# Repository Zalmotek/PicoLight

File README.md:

# PicoLight 🌈

✨ PicoLight is a minimalist adjustable light for low-light photography, based on the Raspberry Pi Pico.

✨ For more details check out the project documentation on [Hackaday](https://hackaday.io/project/182069-picolight-minimalist-light-for-product-shots).

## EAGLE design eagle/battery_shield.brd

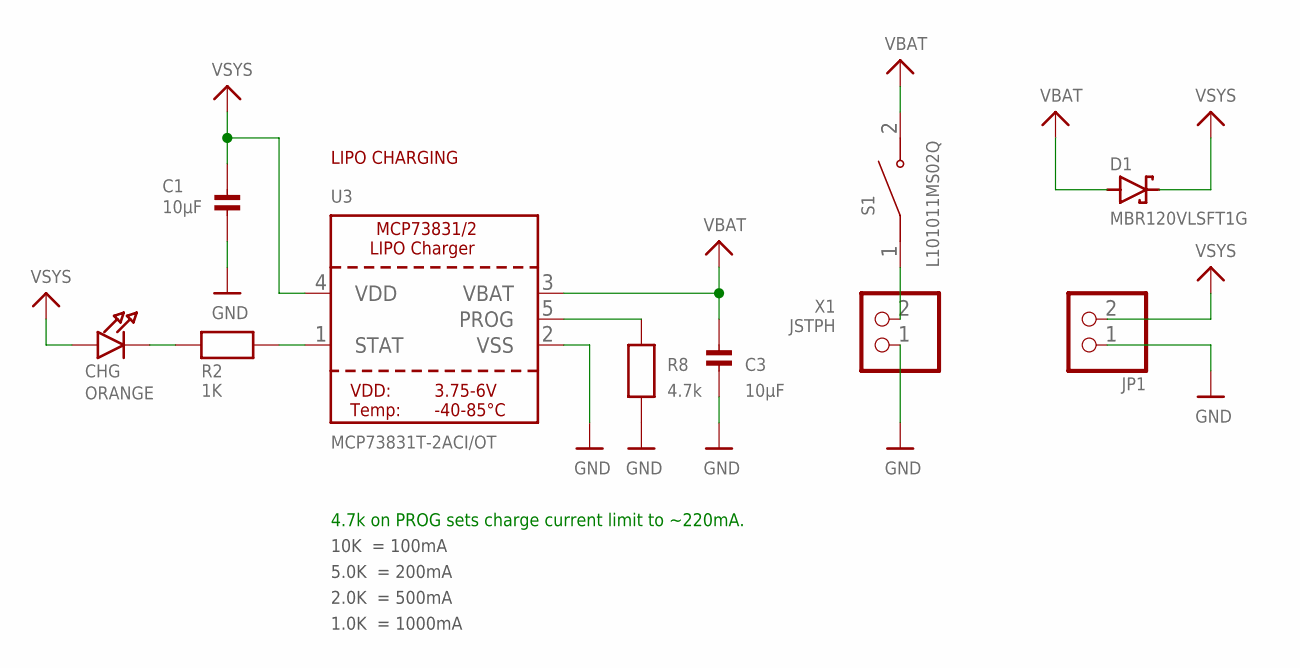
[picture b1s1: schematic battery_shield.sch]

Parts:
C1, C3: 10µF; 0805-NO
CHG: ORANGE; CHIPLED_0805_NOOUTLINE
D1: MBR120VLSFT1G; SOD123FL
JP1: PINHD-1X2; 1X02
R2: 1K; 0603-NO
R8: 4.7k; 0603-NO
S1: L101011MS02Q; SW_L101011MS02Q
U3: MCP73831T-2ACI/OT; SOT23-5
X1: JSTPH; JSTPH2

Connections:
GND: C1.2, C3.2, JP1.1, R8.2, U3.2 (VSS), X1.1
unnamed: CHG.C, R2.1
unnamed: S1.1, X1.2
unnamed: R2.2, U3.1 (STAT)
unnamed: R8.1, U3.5 (PROG)
VBAT: C3.1, D1.A, S1.2, U3.3 (VBAT)
VSYS: C1.1, CHG.A, D1.C, JP1.2, U3.4 (VDD)

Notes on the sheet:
10K = 100mA
5.0K = 200mA
2.0K = 500mA
1.0K = 1000mA
LIPO CHARGING
4.7k on PROG sets charge current limit to ~220mA.

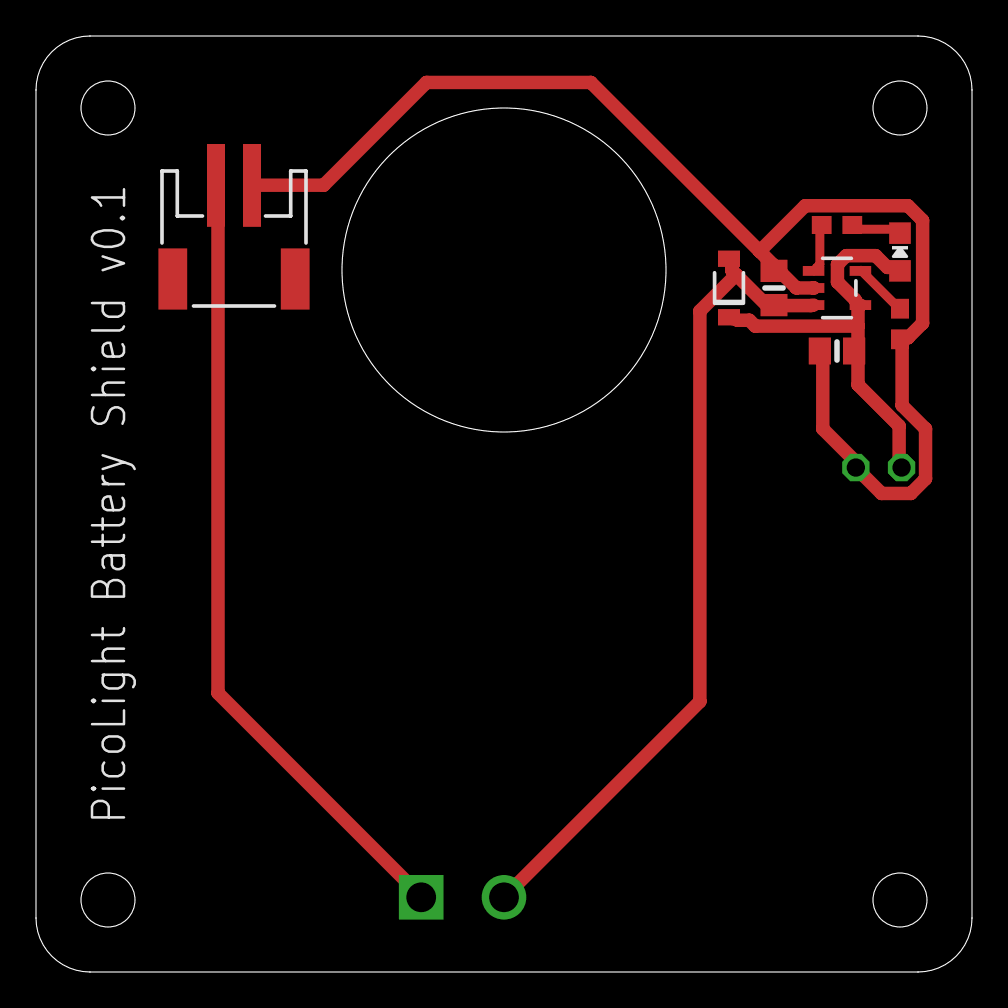
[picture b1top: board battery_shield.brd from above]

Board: 2 copper layers, 52.0 x 52.0 mm, 10 parts (1 on the bottom side), 7 nets.

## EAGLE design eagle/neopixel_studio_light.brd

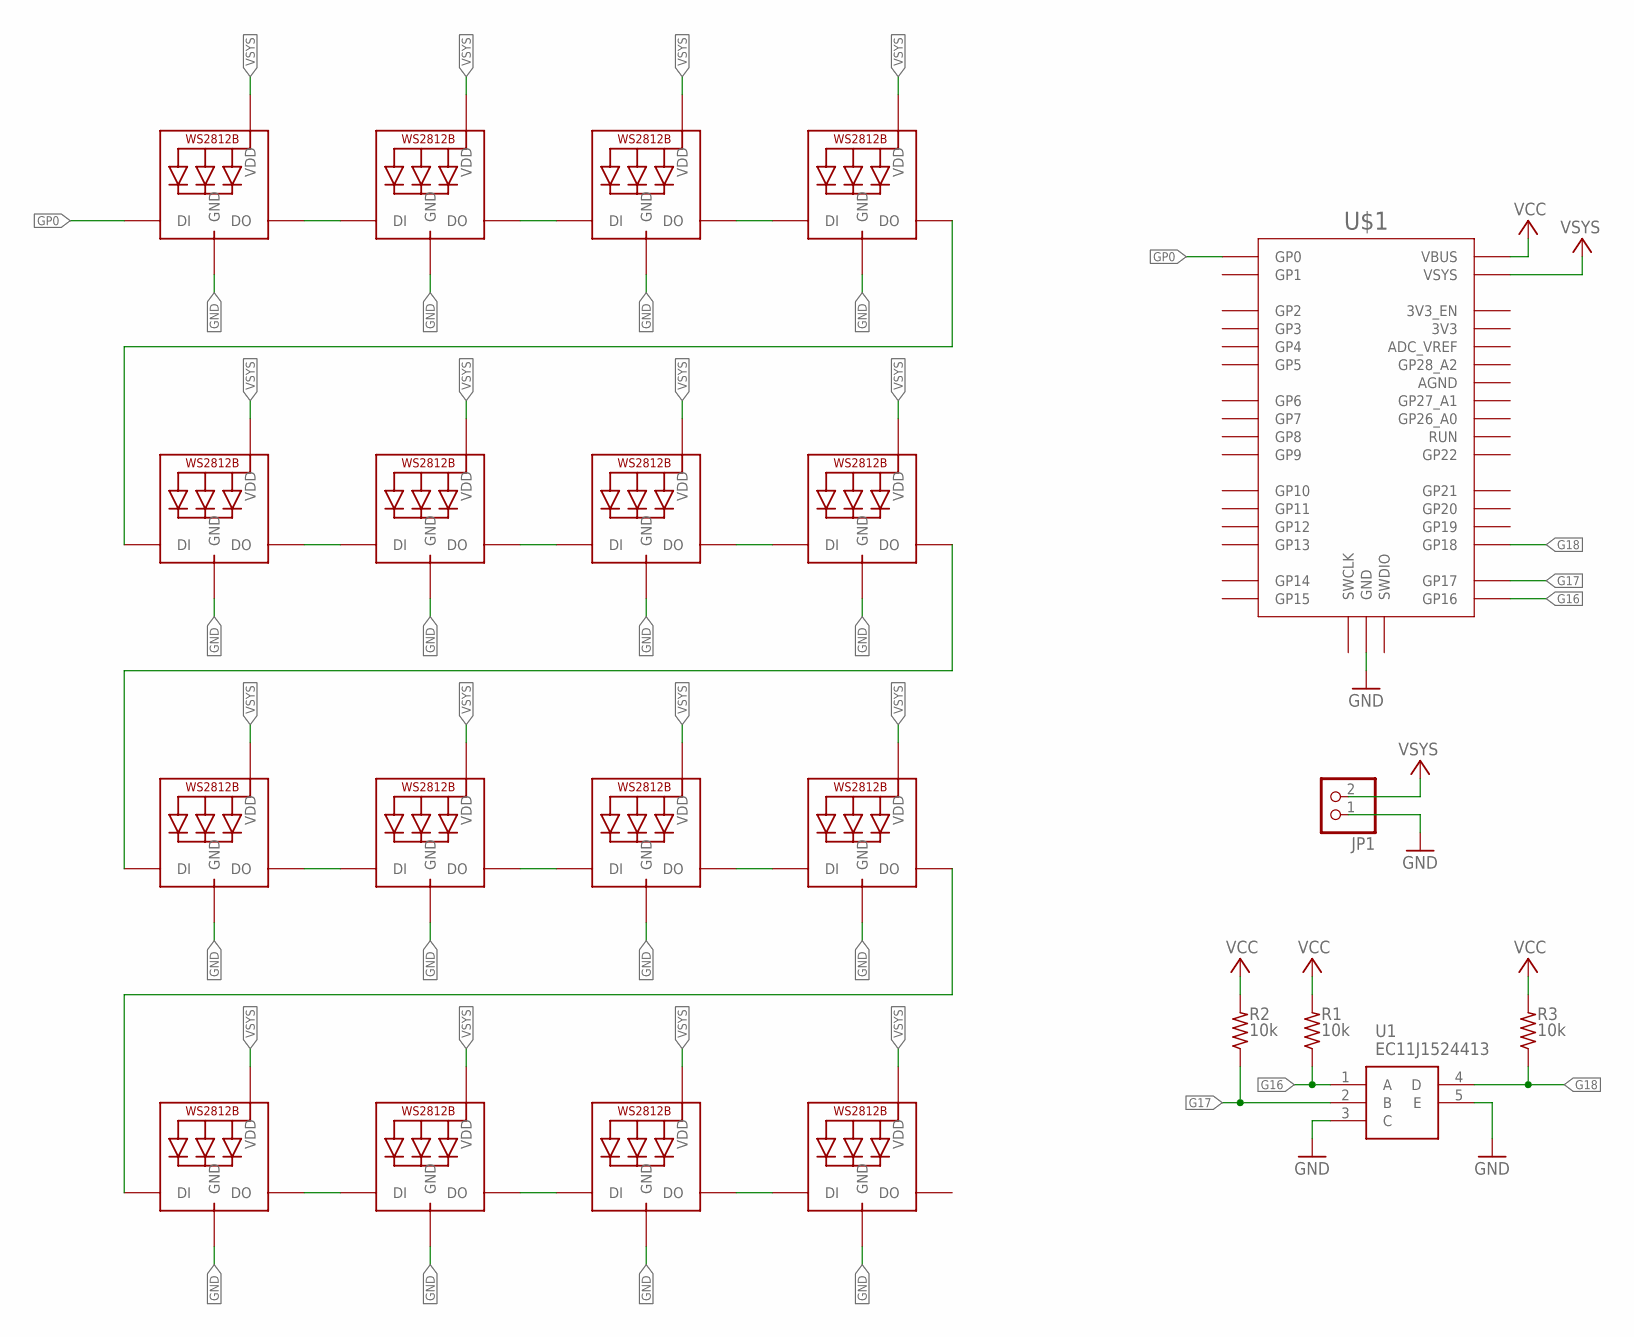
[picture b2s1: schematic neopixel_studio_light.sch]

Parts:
JP1: PINHD-1X2; 1X02
LED1, LED2, LED3, LED4, LED5, LED6, LED7, LED8, LED9, LED10, LED11, LED12, LED13, LED14, LED15, LED16: WS2812B5050; WS2812B
R1, R2, R3: 10k; R0603
U1: EC11J1524413
U$1: RPI_PICO-SMD; RPI_PICO

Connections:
G16: R1.1, U1.1 (A), U$1.GP16
G17: R2.1, U1.2 (B), U$1.GP17
G18: R3.1, U1.4 (D), U$1.GP18
GND: JP1.1, LED1.3-GND (GND), LED2.3-GND (GND), LED3.3-GND (GND), LED4.3-GND (GND), LED5.3-GND (GND), LED6.3-GND (GND), LED7.3-GND (GND), LED8.3-GND (GND), LED9.3-GND (GND), LED10.3-GND (GND), LED11.3-GND (GND), LED12.3-GND (GND), LED13.3-GND (GND), LED14.3-GND (GND), LED15.3-GND (GND), LED16.3-GND (GND), U1.3 (C), U1.5 (E), U$1.GND@1 (GND), U$1.GND@2 (GND), U$1.GND@3 (GND), U$1.GND@4 (GND), U$1.GND@5 (GND), U$1.GND@6 (GND), U$1.GND@7 (GND), U$1.GND@8 (GND)
GP0: LED1.4-DIN (DI), U$1.GP0
unnamed: LED1.2-DOUT (DO), LED2.4-DIN (DI)
unnamed: LED2.2-DOUT (DO), LED3.4-DIN (DI)
unnamed: LED3.2-DOUT (DO), LED4.4-DIN (DI)
unnamed: LED4.2-DOUT (DO), LED5.4-DIN (DI)
unnamed: LED5.2-DOUT (DO), LED6.4-DIN (DI)
unnamed: LED6.2-DOUT (DO), LED7.4-DIN (DI)
unnamed: LED7.2-DOUT (DO), LED8.4-DIN (DI)
unnamed: LED8.2-DOUT (DO), LED9.4-DIN (DI)
unnamed: LED12.2-DOUT (DO), LED13.4-DIN (DI)
unnamed: LED13.2-DOUT (DO), LED14.4-DIN (DI)
unnamed: LED14.2-DOUT (DO), LED15.4-DIN (DI)
unnamed: LED15.2-DOUT (DO), LED16.4-DIN (DI)
unnamed: LED9.2-DOUT (DO), LED10.4-DIN (DI)
unnamed: LED10.2-DOUT (DO), LED11.4-DIN (DI)
unnamed: LED11.2-DOUT (DO), LED12.4-DIN (DI)
VCC: R1.2, R2.2, R3.2, U$1.VBUS
VSYS: JP1.2, LED1.1-VDD (VDD), LED2.1-VDD (VDD), LED3.1-VDD (VDD), LED4.1-VDD (VDD), LED5.1-VDD (VDD), LED6.1-VDD (VDD), LED7.1-VDD (VDD), LED8.1-VDD (VDD), LED9.1-VDD (VDD), LED10.1-VDD (VDD), LED11.1-VDD (VDD), LED12.1-VDD (VDD), LED13.1-VDD (VDD), LED14.1-VDD (VDD), LED15.1-VDD (VDD), LED16.1-VDD (VDD), U$1.VSYS

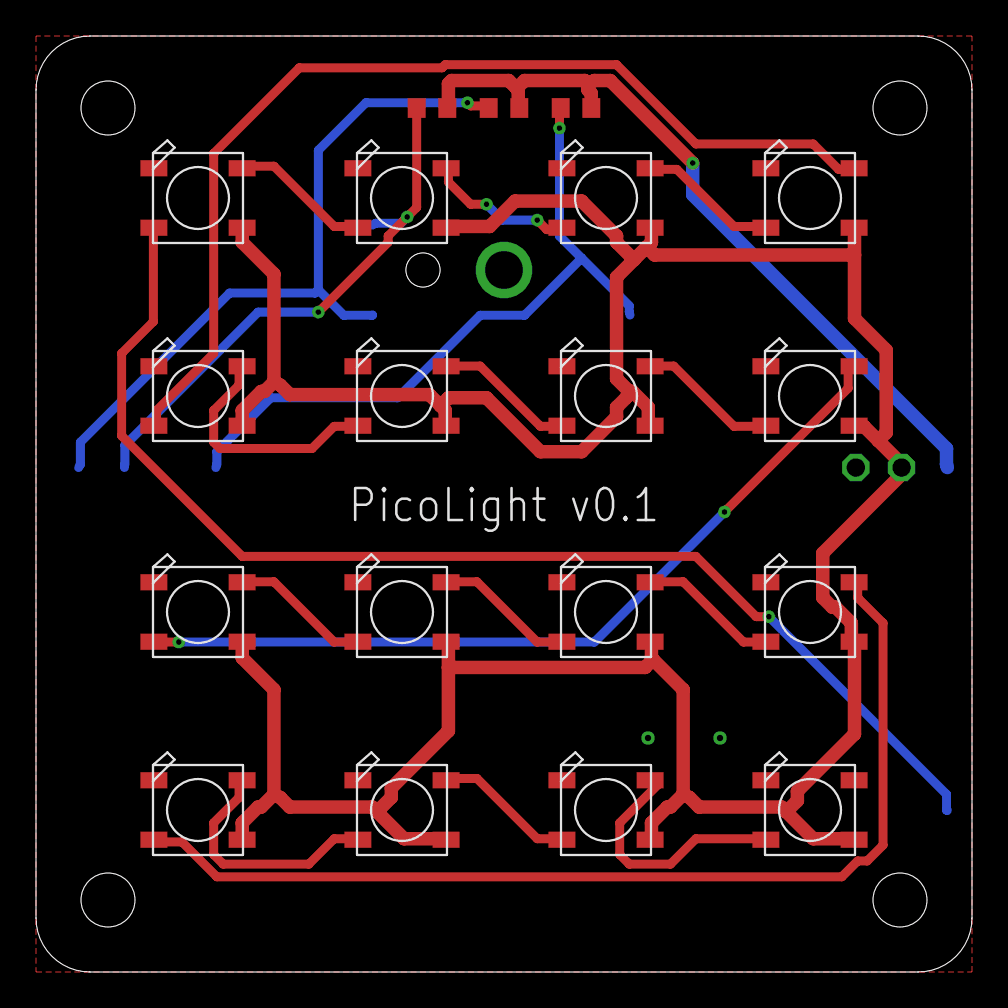
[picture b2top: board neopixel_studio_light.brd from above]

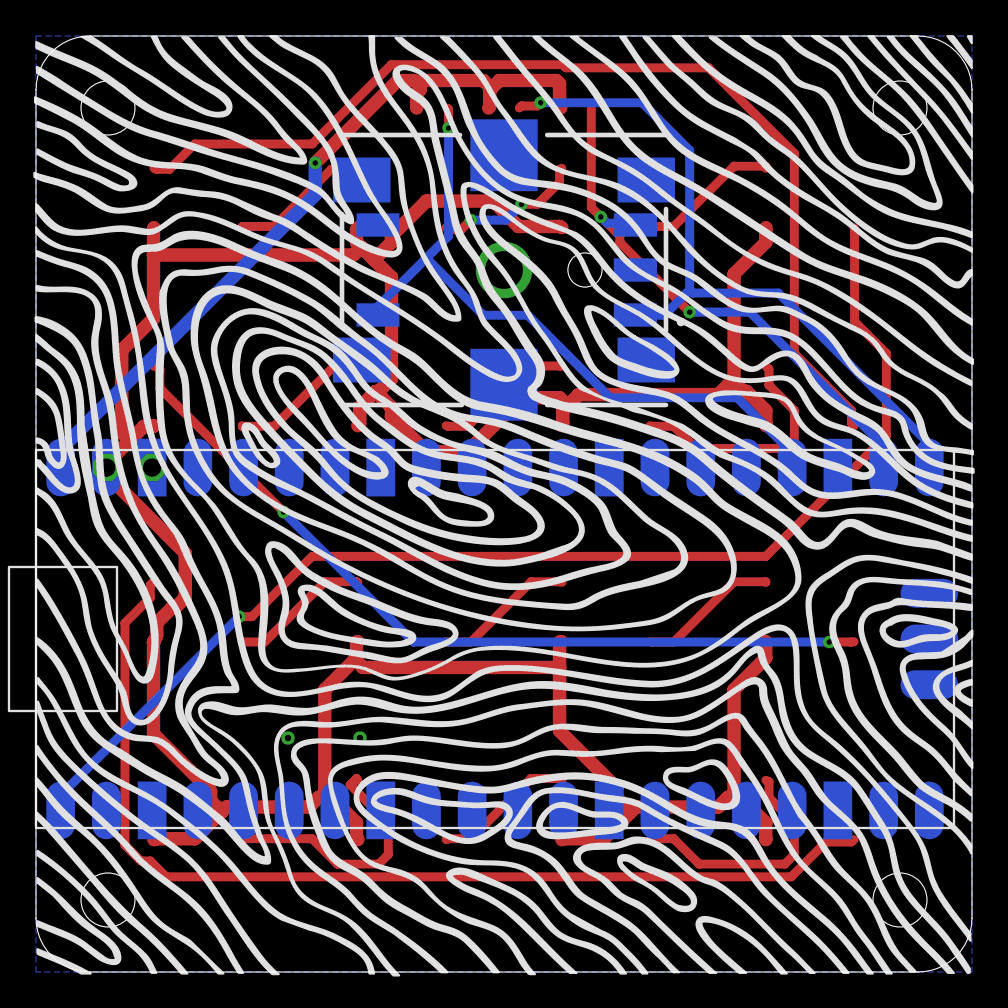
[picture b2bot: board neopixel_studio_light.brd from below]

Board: 2 copper layers, 52.0 x 52.0 mm, 22 parts (2 on the bottom side), 22 nets.

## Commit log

2021-10-04 resized image
2021-10-05 Create LICENSE
2021-10-27 added circuit python libraries + gerber files
2021-11-05 added cover laser cut file
2023-08-21 kicad files, needs mounting holes

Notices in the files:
parts and their libraries:
microbuilder: This work is placed in the public domain, and may be freely used for commercial and non-commercial work with the following conditions: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
